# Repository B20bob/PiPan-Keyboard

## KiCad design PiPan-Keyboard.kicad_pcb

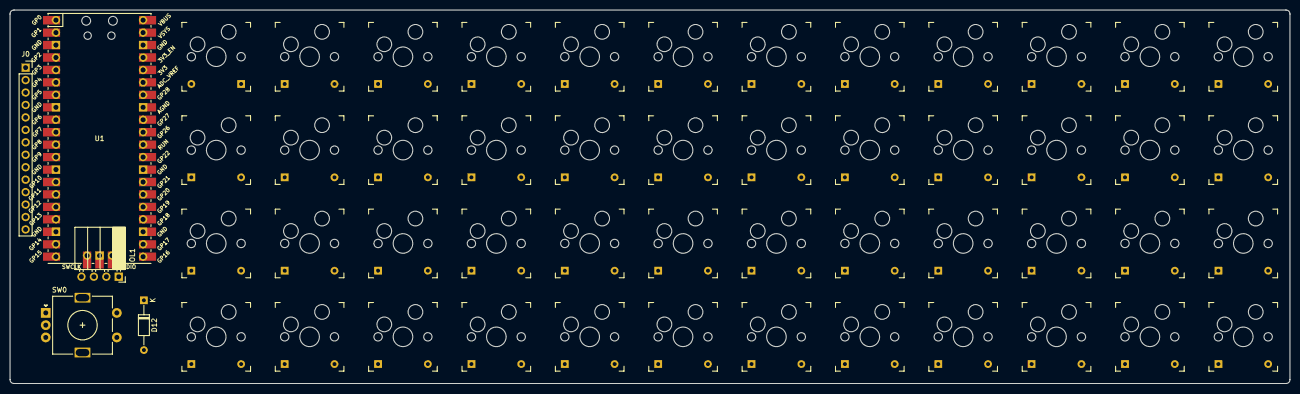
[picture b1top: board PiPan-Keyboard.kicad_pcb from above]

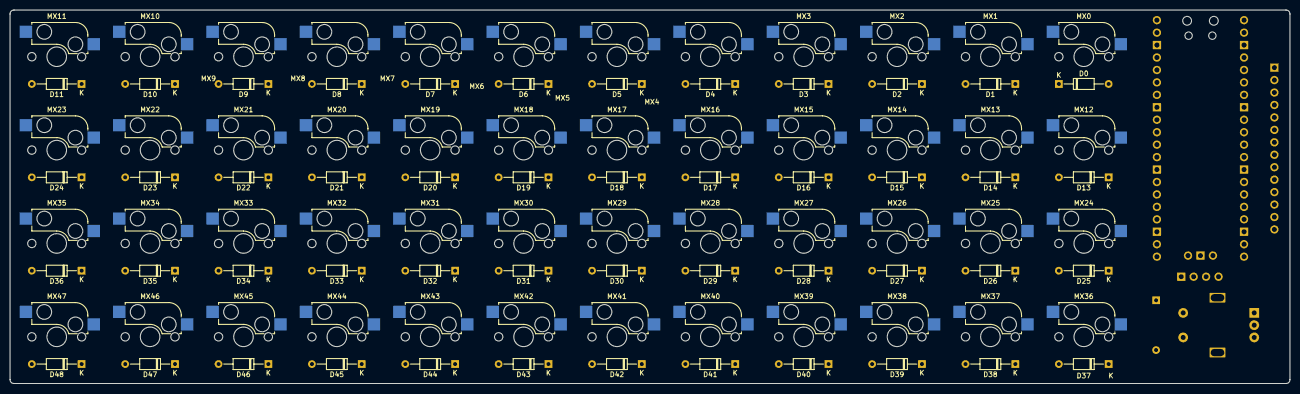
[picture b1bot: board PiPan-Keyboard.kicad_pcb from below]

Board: 2 copper layers, 261.1 x 76.2 mm, 101 parts (48 on the bottom side), 82 nets, no tracks yet.

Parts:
D0, D1, D2, D3, D4, D5, D6, D7, D8, D9, D10, D11, D12, D13, D14, D15, D16, D17, D18, D19, D20, D21, D22, D23, D24, D25, D26, D27, D28, D29, D30, D31, D32, D33, D34, D35, D36, D37, D38, D39, D40, D41, D42, D43, D44, D45, D46, D47, D48: D_Small; D_DO-35_SOD27_P10.16mm_Horizontal
J0: Conn_01x18_MountingPin; PinSocket_1x14_P2.54mm_Vertical
MX0, MX1, MX2, MX3, MX4, MX5, MX6, MX7, MX8, MX9, MX10, MX11, MX12, MX13, MX14, MX15, MX16, MX17, MX18, MX19, MX20, MX21, MX22, MX23, MX24, MX25, MX26, MX27, MX28, MX29, MX30, MX31, MX32, MX33, MX34, MX35, MX36, MX37, MX38, MX39, MX40, MX41, MX42, MX43, MX44, MX45, MX46, MX47: MX-NoLED; Kailh_socket_MX-Outlined
OL1: OLED; PinSocket_1x04_P2.54mm_Horizontal
SW0: RotaryEncoder_Switch; RotaryEncoder_Alps_EC11E-Switch_Vertical_H20mm
U1: Pico; RPi_Pico_SMD_TH

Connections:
5V: J0.2, OL1.3 (VCC), U1.40 (VBUS)
COL0: MX0.1 (COL), MX12.1 (COL), MX24.1 (COL), MX36.1 (COL), U1.6 (GPIO4)
COL1: MX1.1 (COL), MX13.1 (COL), MX25.1 (COL), U1.7 (GPIO5)
COL2: MX2.1 (COL), MX14.1 (COL), U1.9 (GPIO6)
COL3: MX3.1 (COL), U1.10 (GPIO7)
COL4: MX4.1 (COL), MX16.1 (COL), MX28.1 (COL), MX40.1 (COL), U1.11 (GPIO8)
COL5: MX5.1 (COL), MX17.1 (COL), MX29.1 (COL), MX41.1 (COL), U1.12 (GPIO9)
COL6: MX6.1 (COL), MX18.1 (COL), MX30.1 (COL), MX42.1 (COL), U1.14 (GPIO10)
COL7: MX7.1 (COL), MX19.1 (COL), MX31.1 (COL), MX43.1 (COL), U1.15 (GPIO11)
COL8: MX8.1 (COL), MX20.1 (COL), MX32.1 (COL), MX44.1 (COL), U1.16 (GPIO12)
COL9: MX9.1 (COL), MX21.1 (COL), MX33.1 (COL), MX45.1 (COL), U1.17 (GPIO13), U1.19 (GPIO14)
COL10: MX10.1 (COL), MX22.1 (COL), MX34.1 (COL), MX46.1 (COL), U1.20 (GPIO15)
COL11: MX11.1 (COL), MX23.1 (COL), MX35.1 (COL), MX47.1 (COL)
Encoder_A: SW0.A, U1.27 (GPIO21)
Encoder_B: SW0.B, U1.26 (GPIO20)
GND: J0.1, OL1.4 (GND), SW0.C, U1.38 (GND)
I2C1-SDA: OL1.1 (SDA), OL1.2 (SCL), U1.31 (GPIO26_ADC0), U1.32 (GPIO27_ADC1)
unnamed: D0.2 (A), MX0.2 (ROW)
unnamed: D1.2 (A), MX1.2 (ROW)
unnamed: D2.2 (A), MX2.2 (ROW)
unnamed: D3.2 (A), MX3.2 (ROW)
unnamed: D4.2 (A), MX4.2 (ROW)
unnamed: D5.2 (A), MX5.2 (ROW)
unnamed: D6.2 (A), MX6.2 (ROW)
unnamed: D7.2 (A), MX7.2 (ROW)
unnamed: D8.2 (A), MX8.2 (ROW)
unnamed: D9.2 (A), MX9.2 (ROW)
unnamed: D10.2 (A), MX10.2 (ROW)
unnamed: D11.2 (A), MX11.2 (ROW)
unnamed: D12.2 (A), SW0.S1
unnamed: D13.2 (A), MX12.2 (ROW)
unnamed: D14.2 (A), MX13.2 (ROW)
unnamed: D15.2 (A), MX14.2 (ROW)
unnamed: D16.2 (A), MX15.2 (ROW)
unnamed: D17.2 (A), MX16.2 (ROW)
unnamed: D18.2 (A), MX17.2 (ROW)
unnamed: D19.2 (A), MX18.2 (ROW)
unnamed: D20.2 (A), MX19.2 (ROW)
unnamed: D21.2 (A), MX20.2 (ROW)
unnamed: D22.2 (A), MX21.2 (ROW)
unnamed: D23.2 (A), MX22.2 (ROW)
unnamed: D24.2 (A), MX23.2 (ROW)
unnamed: D25.2 (A), MX24.2 (ROW)
unnamed: D26.2 (A), MX25.2 (ROW)
unnamed: D27.2 (A), MX26.2 (ROW)
unnamed: D28.2 (A), MX27.2 (ROW)
unnamed: D29.2 (A), MX28.2 (ROW)
unnamed: D30.2 (A), MX29.2 (ROW)
unnamed: D31.2 (A), MX30.2 (ROW)
unnamed: D32.2 (A), MX31.2 (ROW)
unnamed: D33.2 (A), MX32.2 (ROW)
unnamed: D34.2 (A), MX33.2 (ROW)
unnamed: D35.2 (A), MX34.2 (ROW)
unnamed: D36.2 (A), MX35.2 (ROW)
unnamed: D37.2 (A), MX36.2 (ROW)
unnamed: D38.2 (A), MX37.2 (ROW)
unnamed: D39.2 (A), MX38.2 (ROW)
unnamed: D40.2 (A), MX39.2 (ROW)
unnamed: D41.2 (A), MX40.2 (ROW)
unnamed: D42.2 (A), MX41.2 (ROW)
unnamed: D43.2 (A), MX42.2 (ROW)
unnamed: D44.2 (A), MX43.2 (ROW)
unnamed: D45.2 (A), MX44.2 (ROW)
unnamed: D46.2 (A), MX45.2 (ROW)
unnamed: D47.2 (A), MX46.2 (ROW)
unnamed: D48.2 (A), MX47.2 (ROW)
PIN_21: J0.12, U1.21 (GPIO16)
PIN_22: J0.11, U1.22 (GPIO17)
PIN_24: J0.10, U1.24 (GPIO18)
PIN_25: J0.9, U1.25 (GPIO19)
PIN_30: J0.8, U1.30 (RUN)
PIN_33: J0.7, U1.33 (AGND)
PIN_34: J0.6, U1.34 (GPIO28_ADC2)
PIN_35: J0.5, U1.35 (ADC_VREF)
PIN_36: J0.4, U1.36 (3V3)
PIN_37: J0.3, U1.37 (3V3_EN)
PIN_41: J0.13, U1.41 (SWCLK)
PIN_43: J0.14, U1.43 (SWDIO)
ROW0: D0.1 (K), D1.1 (K), D2.1 (K), D3.1 (K), D4.1 (K), D5.1 (K), D6.1 (K), D7.1 (K), D8.1 (K), D9.1 (K), D10.1 (K), D11.1 (K), D12.1 (K), U1.1 (GPIO0)
ROW1: D13.1 (K), D14.1 (K), D15.1 (K), D16.1 (K), D17.1 (K), D18.1 (K), D19.1 (K), D20.1 (K), D21.1 (K), D22.1 (K), D23.1 (K), D24.1 (K), U1.2 (GPIO1)
ROW2: D25.1 (K), D26.1 (K), D27.1 (K), D28.1 (K), D29.1 (K), D30.1 (K), D31.1 (K), D32.1 (K), D33.1 (K), D34.1 (K), D35.1 (K), D36.1 (K), U1.4 (GPIO2)
ROW3: D37.1 (K), D38.1 (K), D39.1 (K), D40.1 (K), D41.1 (K), D42.1 (K), D43.1 (K), D44.1 (K), D45.1 (K), D46.1 (K), D47.1 (K), D48.1 (K), U1.5 (GPIO3)

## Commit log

2023-03-18 Init
2023-03-19 added some submodules
2023-03-19 added some libs
2023-03-20 Started layout
2023-03-20 added digikey lib
2023-03-23 added footprints
2023-03-23 added RGB LEDs to schematic
2023-03-23 added libs and encoder and oled
2023-03-23 blank
2023-04-08 updated definitions
2023-04-09 placed first row
2023-04-10 corrected switches in schema
2023-04-10 corrected neopixels
2023-04-10 updated PCB with added components
2023-04-13 fixing diode labels in progress.
2023-04-16 placed diodes
2023-04-16 generated first test step file
2023-04-18 added outline to kaihl mx footprint andfixedlayout
2023-04-18 changed .step to loose tolorances to test
2023-04-18 Rendered Font and rear images
2023-04-22 sync
2023-04-22 adjusted board size and pico position
2023-04-22 updated .step to current iteration
2023-04-22 removed outdated .stl
2023-04-22 moved encoder and updated .step
2023-04-22 moved encoder
2023-04-22 moved encoder again
2023-04-22 moved OLED and generated new .step
2023-04-22 moved encoder diode
2023-04-22 expanded left edge of pcb, generated new .step
